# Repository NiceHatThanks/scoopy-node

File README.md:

# Scoopy Node

Tiny, local-first room hardware for Home Assistant and ESPHome.

Scoopy is a compact USB-C powered room controller built around an ESP32-C3. V1 combines two physical buttons, three PWM LEDs, optional LD2410C mmWave presence sensing, optional Home Assistant Bluetooth Proxy support, and an I²C expansion connection in a small 3D-printed enclosure.

There are two enclosure variants:

- **Scoopy Presence** — the full-size enclosure with an LD2410C mmWave presence sensor.
- **Scoopy Compact** — the smaller enclosure without the radar.

Both variants use the same firmware image. If an LD2410C is not fitted, the rest of Scoopy continues to work normally.

This repository contains the source-available hardware files, versioned STL enclosure exports, ESPHome firmware, captive-portal UI, manufacturing outputs, and project documentation.

## Quick links

- Website and product information: https://nicehatthanks.com
- First-time setup: https://nicehatthanks.com/setup/
- Interactive Home Assistant docs and examples: https://nicehatthanks.com/docs/
- Assembly guide: [`docs/assembly.md`](docs/assembly.md)
- Troubleshooting: [`docs/troubleshooting.md`](docs/troubleshooting.md)
- Bambu Studio / 3MF project: [Scoopy on MakerWorld](https://makerworld.com/en/models/3231250-scoopy-home-assistant-esphome-room-controller#profileId-3659818)

## Repository structure

```text
hardware/
  kicad/             Editable KiCad source files
  gerbers/           Fabrication-ready Gerbers and drill files
  bom/               Bill of materials and manufacturing exports

enclosure/
  compact/           Versioned STL exports for Scoopy Compact
  presence/          Versioned STL exports for Scoopy Presence
  build/             Assembly photos used by the build guide

firmware/
  esphome/           Unified ESPHome configuration and custom components
  captive-portal/    Source for the branded Wi-Fi setup page

docs/
  setup.md           First-time setup and Home Assistant pairing
  examples.md        Ready-made Home Assistant automations
  assembly.md        V1 enclosure assembly guide
  troubleshooting.md Common setup, firmware and hardware issues
```

## Firmware

`firmware/esphome/scoopy.yaml` is the unified production configuration for both Scoopy variants. The V1 firmware identifies itself as `1.0.0` through the ESPHome project version.

V1 features include:

- Unique `scoopy-XXXXXX` naming using the ESP32 MAC address
- Scoopy-branded local Wi-Fi provisioning with a captive portal
- ESPHome native API and Home Assistant discovery
- Two physical buttons exposed as `single`, `double`, and `hold` event entities
- Three individually dimmable PWM LED entities
- Individual pulse, flash, and alert LED effects
- Coordinated three-LED patterns including Circular Pulse, Comet, Breathe All, Heartbeat, Ping Pong, and Ripple
- Pulsing red Wi-Fi/setup indication and a brief green confirmation after connection
- LD2410C presence, moving-target, and still-target entities when the radar is fitted
- Optional Home Assistant Bluetooth Proxy, disabled by default
- Passive BLE scanning with one active proxy connection slot
- Website-hosted firmware updates through the Home Assistant **Firmware Update** entity
- Native ESPHome OTA support for local/development updates
- USB serial provisioning through Improv
- Wi-Fi signal, Wi-Fi percentage, IP address, uptime, ESPHome version, and Scoopy firmware diagnostics
- I²C expansion on GPIO5 (SDA) and GPIO7 (SCL)
- Physical Wi-Fi/factory recovery by holding both buttons for 10 seconds

The firmware deliberately uses one image for both variants. On Scoopy Compact, LD2410C entities may show as unavailable or Unknown because the radar is not fitted; this does not affect buttons, LEDs, Wi-Fi, OTA, Bluetooth Proxy, or the rest of the device.

## Home Assistant

Once Scoopy has joined the same network as Home Assistant, ESPHome discovery should find it automatically.

Ready-made automations are in [`docs/examples.md`](docs/examples.md). The examples cover:

- LED pattern control
- Button-controlled lighting
- Presence-controlled lighting
- Time-aware lighting
- Alarm reminders
- Status LEDs
- Multi-function room controls for lights, fans, and blinds

The interactive version at https://nicehatthanks.com/docs/ can take one of your Scoopy Entity IDs and fill the matching Scoopy prefix into the examples automatically.

## Setup and recovery

For normal first-time setup, use https://nicehatthanks.com/setup/ or [`docs/setup.md`](docs/setup.md).

A fresh or factory-reset Scoopy creates a Wi-Fi network named `scoopy-XXXXXX` with password `scoopy123`. Wi-Fi credentials are sent directly to Scoopy through its local setup page; no Scoopy cloud account is involved.

To clear saved Wi-Fi credentials and return to setup mode, hold both physical buttons together for 10 seconds. The middle red LED flashes rapidly near the end of the hold before the reset is performed.

## Firmware updates

Released firmware can be installed directly from Home Assistant through Scoopy's **Firmware Update** entity. Scoopy reads the update manifest hosted at:

`https://nicehatthanks.com/firmware/scoopy/manifest.json`

An OTA update preserves the device identity, saved Wi-Fi credentials, Home Assistant connection, and existing entity IDs.

## Enclosure and printing

GitHub contains the versioned raw STL exports for Scoopy Compact and Scoopy Presence.

The slicer-ready Bambu Studio / 3MF project is intentionally **not** duplicated in this repository. MakerWorld is the single maintained source for the Bambu project and print profile:

**[Scoopy on MakerWorld](https://makerworld.com/en/models/3231250-scoopy-home-assistant-esphome-room-controller#profileId-3659818)**

See [`enclosure/README.md`](enclosure/README.md) for the STL layout and [`docs/assembly.md`](docs/assembly.md) for assembly.

## Hardware overview

V1 uses a 28 × 28 mm carrier PCBA with:

- ESP32-C3 Super Mini
- 2 × tactile buttons
- 3 × LEDs with 2.2 kΩ series resistors
- Optional HLK-LD2410C mmWave presence sensor
- I²C expansion connection
- USB-C power through the ESP32-C3 module

Scoopy Presence uses the LD2410C and the larger enclosure. Scoopy Compact uses the same carrier and firmware without the radar.

Electrical design and manufacturing files are documented in [`hardware/README.md`](hardware/README.md).

## Assembly

The enclosure build is the same basic process for Compact and Presence: fit the heat-set insert, secure the PCBA, place the two buttons in the lid, then clip the base and lid together while aligning the three light pipes with the LEDs.

For Scoopy Presence, a nylon M2 screw is recommended near the LD2410C because a metal screw may affect the radar.

See the illustrated [`docs/assembly.md`](docs/assembly.md) guide.

## Release status

`v1.0.0` is the first formal Scoopy release. The V1 hardware, firmware, STL exports, documentation, and manufacturing files in that release tag form the reproducible V1 baseline.

Development on `main` may move ahead after the release. Use a release tag when reproducing a known version.

## Build your own

The hardware, firmware, and printable STL files are available so you can inspect Scoopy, build one for yourself, modify it, and experiment with your own non-commercial versions.

Commercial manufacture or sale requires prior permission from Nice Hat Thanks.

See [`LICENSE`](LICENSE) for the full terms.

## Licence

Scoopy is **source available for personal and non-commercial use**. You may inspect the files, build your own, modify them, and share non-commercial derivatives under the terms in [`LICENSE`](LICENSE).

Commercial manufacture, sale, or other commercial use requires prior written permission from Nice Hat Thanks.

Scoopy is not released under an open-source or open-hardware licence.

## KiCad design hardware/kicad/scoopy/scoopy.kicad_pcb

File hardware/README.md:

# Hardware

Electrical design and manufacturing files for Scoopy Node.

## Structure

- `kicad/scoopy/` — editable KiCad project source
- `gerbers/v1/` — V1 fabrication-ready Gerber and drill files
- `gerbers/V1-Gerbers.zip` — upload-ready V1 Gerber archive
- `bom/v1/` — V1 bill of materials and manufacturing exports

The KiCad directory contains the editable design source. Generated fabrication outputs live separately so the project stays clean and manufacturing files are easy to identify.

Exported schematic PDFs are not currently committed as a separate directory. The editable schematic is part of the KiCad project; release-specific exports can be added when useful.

Third-party STEP/GLB models and standalone library components with redistribution restrictions are intentionally not included.

## Revisions

Manufacturing outputs should remain grouped by hardware revision (`v1/`, `v2/`, and so on). Releases and Git tags can then identify the exact set of files used for a known hardware build.

`v1.0.0` identifies the first production-frozen V1 hardware baseline. Development on `main` may continue after that tag, so use a release/tag when reproducing a known hardware build.

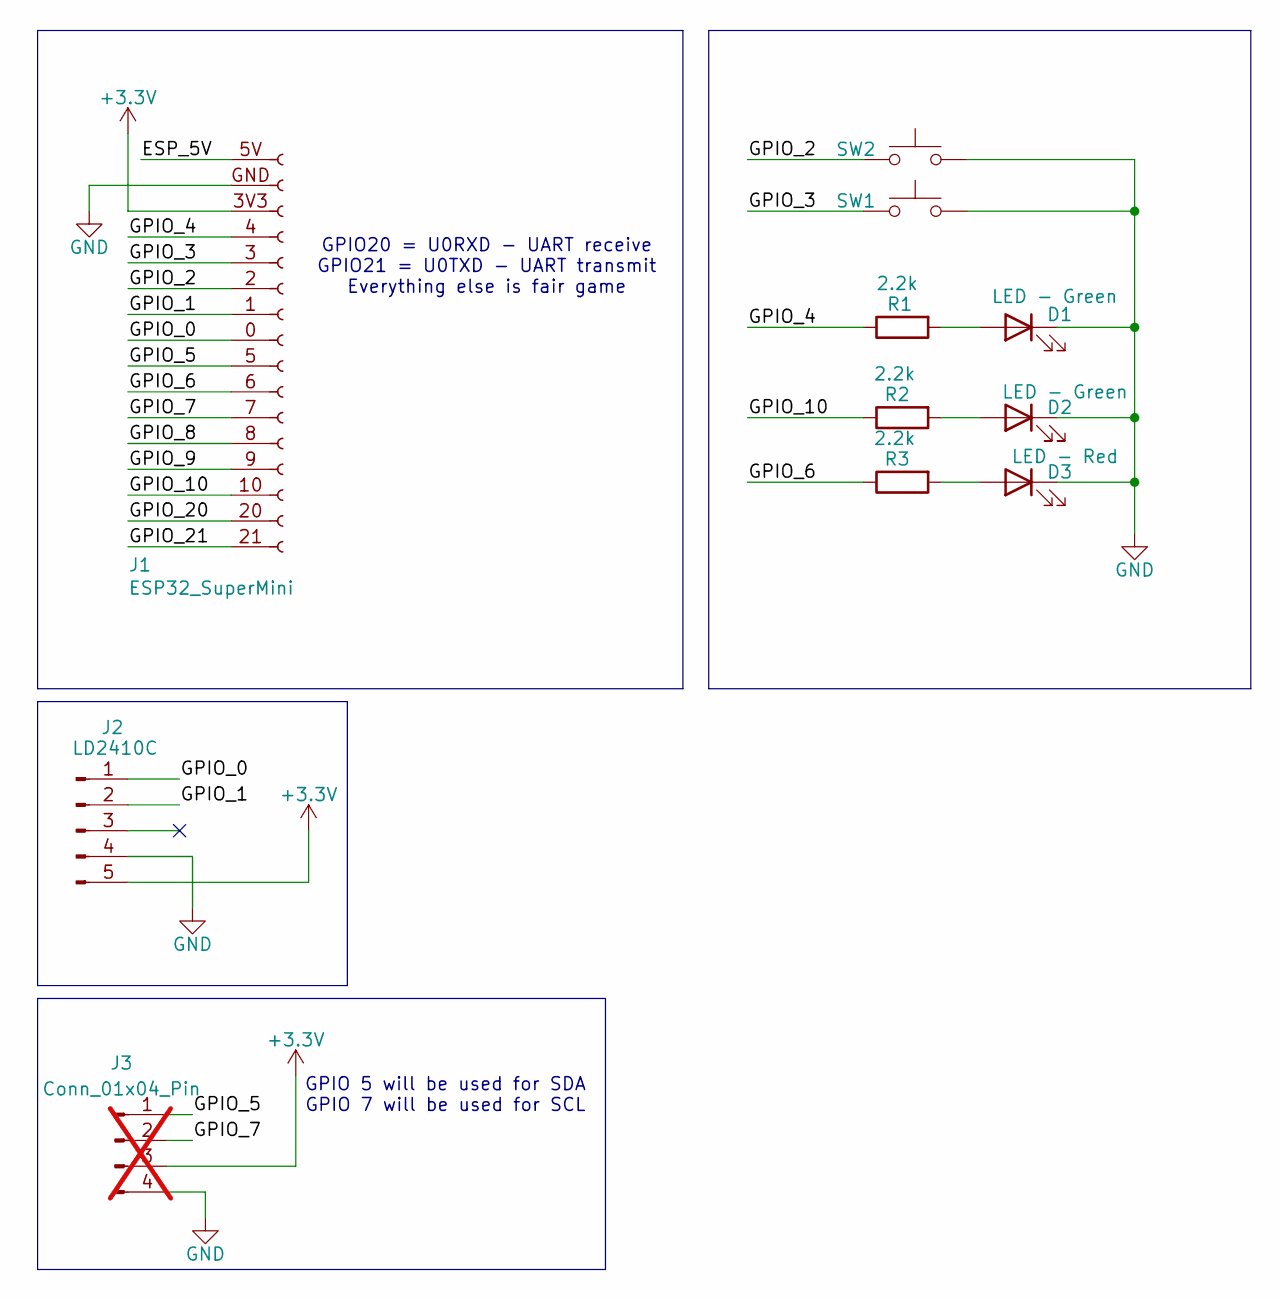
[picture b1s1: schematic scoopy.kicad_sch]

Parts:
D1, D2: LED - Green; LED_0603_1608Metric; MPN C22371297
D3: LED - Red; LED_0603_1608Metric; MPN C19171390
J1: ESP32_SuperMini; ESP32-C3-SuperMini
J2: LD2410C; Ld2410c; MPN C19723500
J3: Conn_01x04_Pin; PinHeader_1x04_P2.54mm_Vertical; not fitted
R1, R2, R3: 2.2k; R_0603_1608Metric; MPN C2907005
SW1, SW2: SW_Push; SW_SPST_TL3305C; MPN C879462

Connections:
+3.3V: J1.3V3 (Pin_3), J2.5, J3.3
/ESP_5V: J1.5V (Pin_1)
/GPIO_0: J1.0 (Pin_8), J2.1
/GPIO_1: J1.1 (Pin_7), J2.2
/GPIO_2: J1.2 (Pin_6), SW2.1
/GPIO_3: J1.3 (Pin_5), SW1.1
/GPIO_4: J1.4, R1.1
/GPIO_5: J1.5 (Pin_9), J3.1
/GPIO_6: J1.6 (Pin_10), R3.1
/GPIO_7: J1.7 (Pin_11), J3.2
/GPIO_8: J1.8 (Pin_12)
/GPIO_9: J1.9 (Pin_13)
/GPIO_10: J1.10 (Pin_14), R2.1
/GPIO_20: J1.20 (Pin_15)
/GPIO_21: J1.21 (Pin_16)
GND: D1.1 (K), D2.1 (K), D3.1 (K), J1.GND (Pin_2), J2.4, J3.4, SW1.2, SW2.2
unnamed: D1.2 (A), R1.2
unnamed: D2.2 (A), R2.2
unnamed: D3.2 (A), R3.2

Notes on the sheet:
GPIO 5 will be used for SDA GPIO 7 will be used for SCL
GPIO20 = U0RXD - UART receive GPIO21 = U0TXD - UART transmit Everything else is fair game

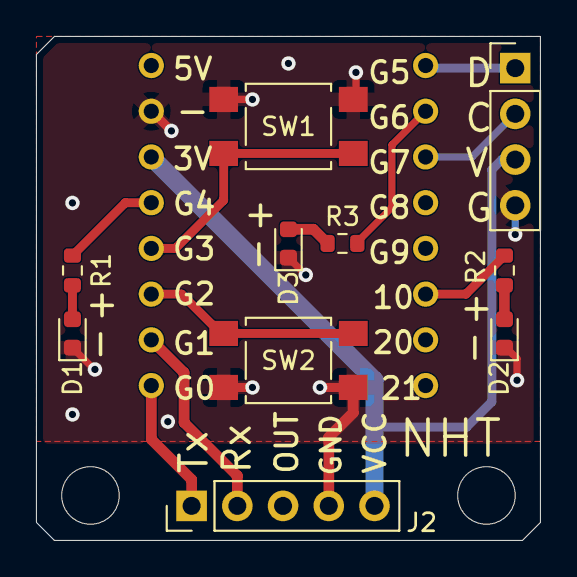
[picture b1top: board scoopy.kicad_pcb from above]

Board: 2 copper layers, 28.0 x 28.0 mm, 11 parts (1 on the bottom side), 14 nets.
